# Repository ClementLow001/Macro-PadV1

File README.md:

# Macro-PadV1

MacroPad PCB was designed using KiCAD, Firmware is written in KMK

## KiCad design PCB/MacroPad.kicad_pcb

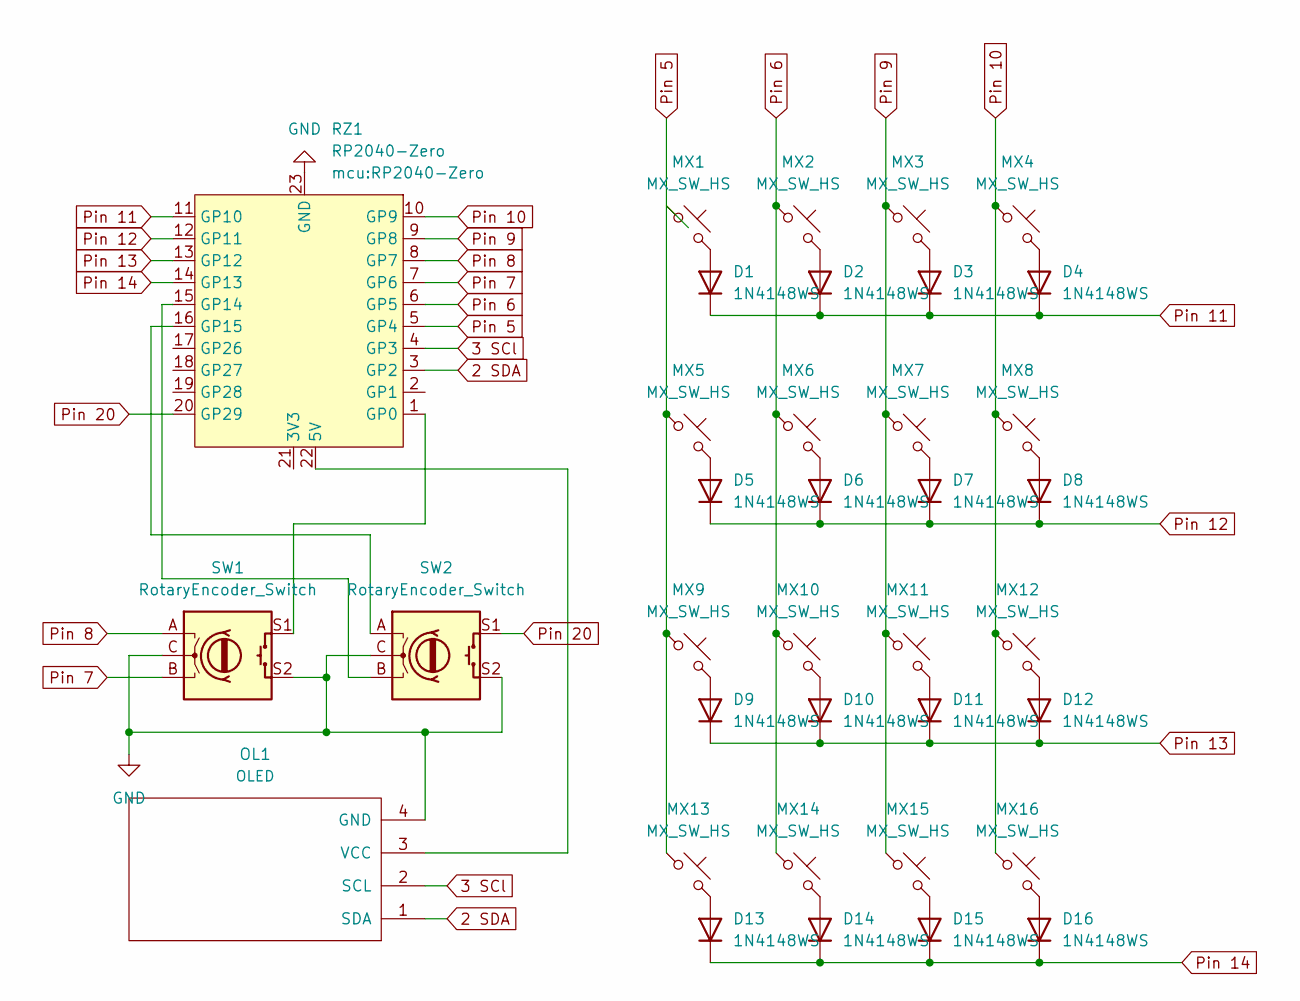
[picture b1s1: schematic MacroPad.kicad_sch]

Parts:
D1, D2, D3, D4, D5, D6, D7, D8, D9, D10, D11, D12, D13, D14, D15, D16: 1N4148WS; D_SOD-323
MX1, MX2, MX3, MX4, MX5, MX6, MX7, MX8, MX9, MX10, MX11, MX12, MX13, MX14, MX15, MX16: MX_SW_HS; SW_MX_HS_CPG151101S11_1u
OL1: OLED
RZ1: RP2040-Zero
SW1, SW2: RotaryEncoder_Switch; ROT_Alps_EC11E-Switch

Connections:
2 SDA: OL1.1 (SDA), RZ1.3 (GP2)
3 SCl: OL1.2 (SCL), RZ1.4 (GP3)
GND: OL1.4 (GND), RZ1.23 (GND), SW1.C, SW1.S2, SW2.C, SW2.S2
unnamed: D1.2 (A), MX1.2
unnamed: D2.2 (A), MX2.2
unnamed: D3.2 (A), MX3.2
unnamed: D4.2 (A), MX4.2
unnamed: D5.2 (A), MX5.2
unnamed: D6.2 (A), MX6.2
unnamed: D7.2 (A), MX7.2
unnamed: D8.2 (A), MX8.2
unnamed: D9.2 (A), MX9.2
unnamed: D10.2 (A), MX10.2
unnamed: D11.2 (A), MX11.2
unnamed: D12.2 (A), MX12.2
unnamed: D13.2 (A), MX13.2
unnamed: D14.2 (A), MX14.2
unnamed: D15.2 (A), MX15.2
unnamed: D16.2 (A), MX16.2
unnamed: OL1.3 (VCC), RZ1.22 (5V)
unnamed: RZ1.1 (GP0), SW1.S1
unnamed: RZ1.15 (GP14), SW2.B
unnamed: RZ1.16 (GP15), SW2.A
Pin 5: MX1.1, MX5.1, MX9.1, MX13.1, RZ1.5 (GP4)
Pin 6: MX2.1, MX6.1, MX10.1, MX14.1, RZ1.6 (GP5)
Pin 7: RZ1.7 (GP6), SW1.B
Pin 8: RZ1.8 (GP7), SW1.A
Pin 9: MX3.1, MX7.1, MX11.1, MX15.1, RZ1.9 (GP8)
Pin 10: MX4.1, MX8.1, MX12.1, MX16.1, RZ1.10 (GP9)
Pin 11: D1.1 (K), D2.1 (K), D3.1 (K), D4.1 (K), RZ1.11 (GP10)
Pin 12: D5.1 (K), D6.1 (K), D7.1 (K), D8.1 (K), RZ1.12 (GP11)
Pin 13: D9.1 (K), D10.1 (K), D11.1 (K), D12.1 (K), RZ1.13 (GP12)
Pin 14: D13.1 (K), D14.1 (K), D15.1 (K), D16.1 (K), RZ1.14 (GP13)
Pin 20: RZ1.20 (GP29), SW2.S1

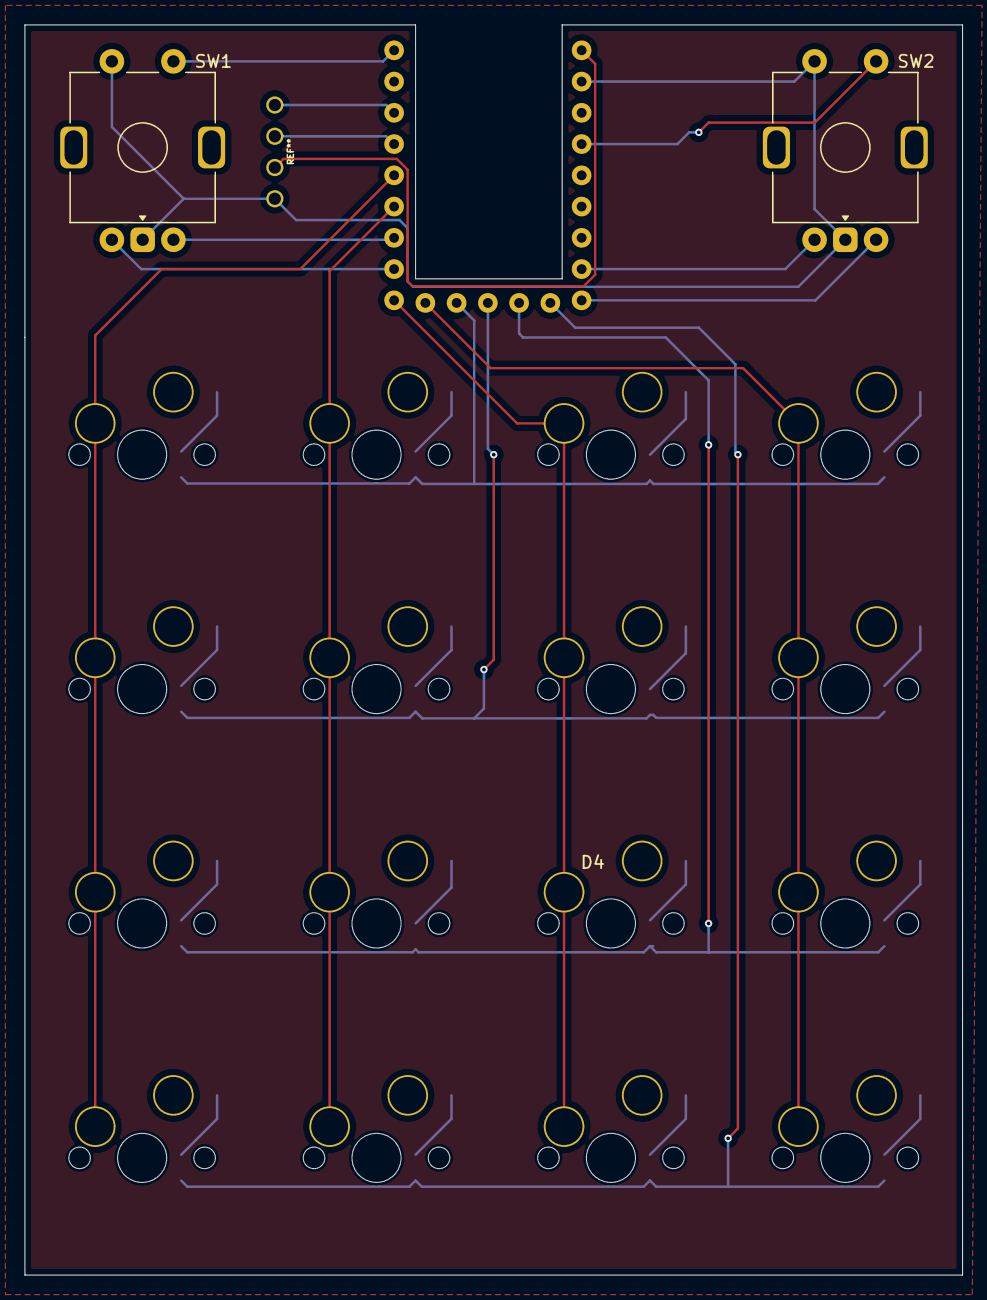
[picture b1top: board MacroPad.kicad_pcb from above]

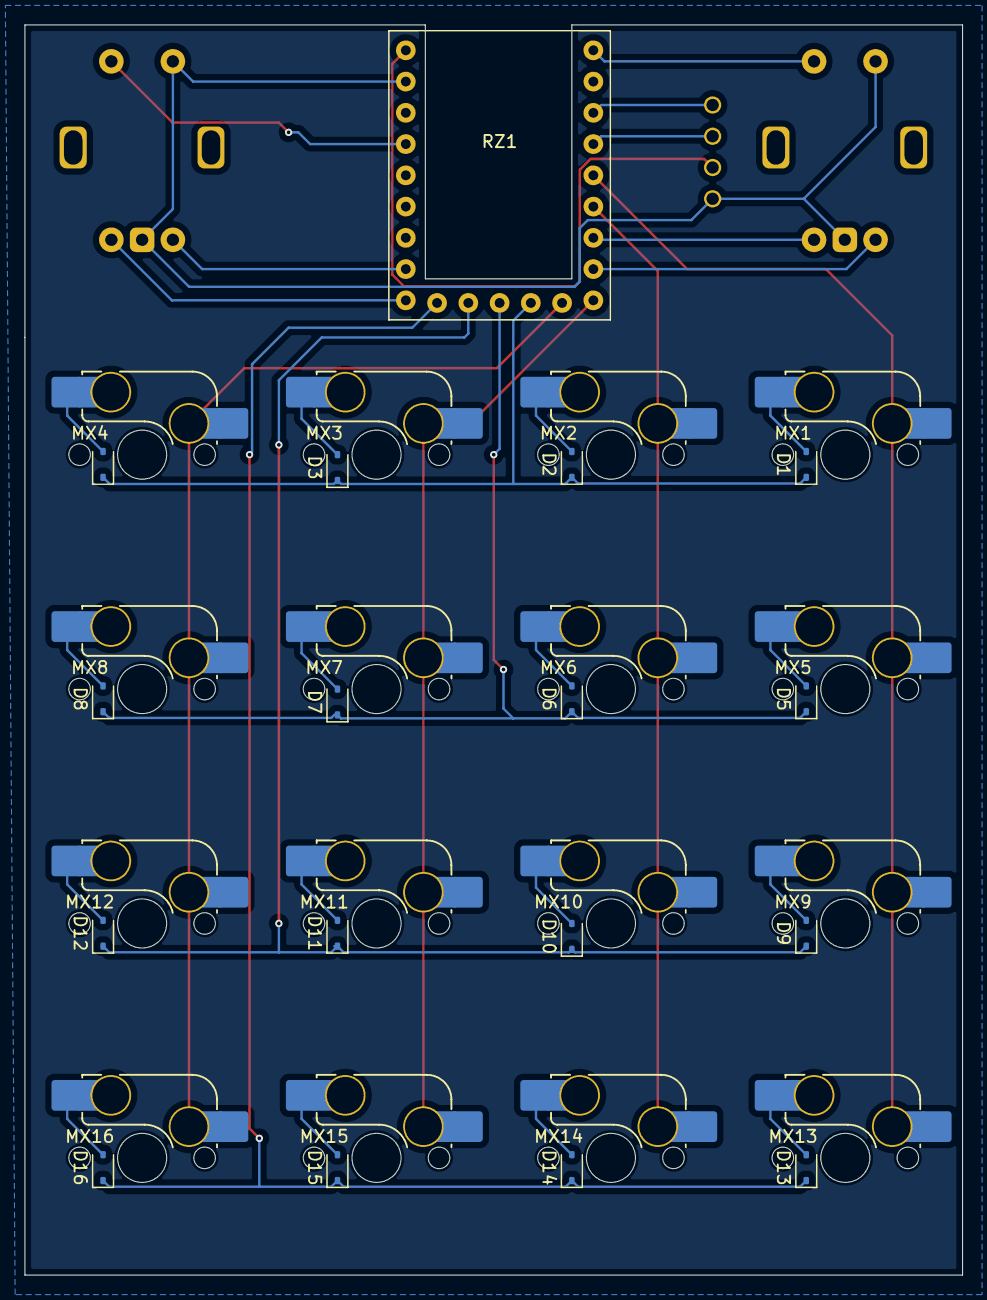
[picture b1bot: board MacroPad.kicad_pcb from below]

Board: 2 copper layers, 76.2 x 101.6 mm, 36 parts (33 on the bottom side), 34 nets.

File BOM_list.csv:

designator,quantity,value,pack,mpn,mount_type
"D1, D10, D11, D12, D13, D14, D15, D16, D2, D3, D4, D5, D6, D7, D8, D9",16,1N4148WS,D_SOD-323,,smt
"MX1, MX10, MX11, MX12, MX13, MX14, MX15, MX16, MX2, MX3, MX4, MX5, MX6, MX7, MX8, MX9",16,MX_SW_HS,SW_MX_HS_CPG151101S11_1u,,smt
OL1,1,OLED,OLED,,tht
RZ1,1,RP2040-Zero,RP2040-Zero,,tht
"SW1, SW2",2,RotaryEncoder_Switch,ROT_Alps_EC11E-Switch,,tht

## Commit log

2025-04-17 Create Firmware
